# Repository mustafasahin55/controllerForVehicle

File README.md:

# STM32 Tabanlı Motor Kontrol Kartı Özellikleri ve Bağlantıları

## Donanım Özellikleri
1. **PCB Katman Yapısı**:
   1. Katman: Sinyal iletimi için tasarlanmış bakır izler
   2. Katman: Toprak düzlemi (GND)
   3. Katman: Güç dağıtım katmanı (5V/12V)
   4. Katman: İkincil sinyal iletim katmanı

2. **Ana Bileşenler**:
   - STM32F4 serisi mikrodenetleyici (ARM Cortex-M4 çekirdek)
   - PCA9685PW 16-kanallı PWM sürücü entegresi
   - MPU6050 6-eksen IMU sensör (Jiroskop + İvmeölçer)
   - 3x L298N çift motor sürücü modülü

3. **Teknik Parametreler**:
   - PWM Çözünürlüğü: 12-bit (4096 adım)
   - Maksimum Motor Akımı: 2A/channel
   - I2C Haberleşme Hızı: 100kHz/400kHz
   - Çalışma Voltajı: 7-12V DC

## Bağlantı Konfigürasyonu

### STM32-PCA9685PW Arası Bağlantılar
| PCA9685 Pin | STM32 Pin   | İşlev       |
|-------------|-------------|-------------|
| PCA_SCL     | PB6         | I2C1 Clock  |
| PCA_SDA     | PB7         | I2C1 Data   |
| VCC         | 5V          | Güç Besleme|
| GND         | GND         | Toprak      |

### STM32-MPU6050 Arası Bağlantılar
| MPU6050 Pin | STM32 Pin   | İşlev       |
|-------------|-------------|-------------|
| SDA         | PB11        | I2C2 Data   |
| SCL         | PB10        | I2C2 Clock  |
| VCC         | 3.3V        | Güç Besleme|
| GND         | GND         | Toprak      |

### Motor Sürücü Bağlantıları
| L298N Pin   | Bağlantı Noktası | Açıklama               |
|-------------|-------------------|-----------------------|
| IN1-4       | PCA9685 PWM0-3    | Motor kontrol sinyali|
| ENA/ENB     | 5V                | Enable sabit aktif    |
| OUT1-4      | Motor Terminalleri| Motor çıkışları      |
| 12V         | Güç Girişi        | Harici güç kaynağı    |

## Pinout Tablosu
| STM32 Pin | Bağlı Bileşen | İşlev              |
|-----------|---------------|--------------------|
| PA0       | Seri Debug    | UART1_TX           |
| PA1       | Seri Debug    | UART1_RX           |
| PB6-7     | PCA9685       | I2C1 SCL/SDA       |
| PB10-11   | MPU6050       | I2C2 SCL/SDA       |
| PC6-9     | LED Göstergeler| Sistem Durum LED'leri|

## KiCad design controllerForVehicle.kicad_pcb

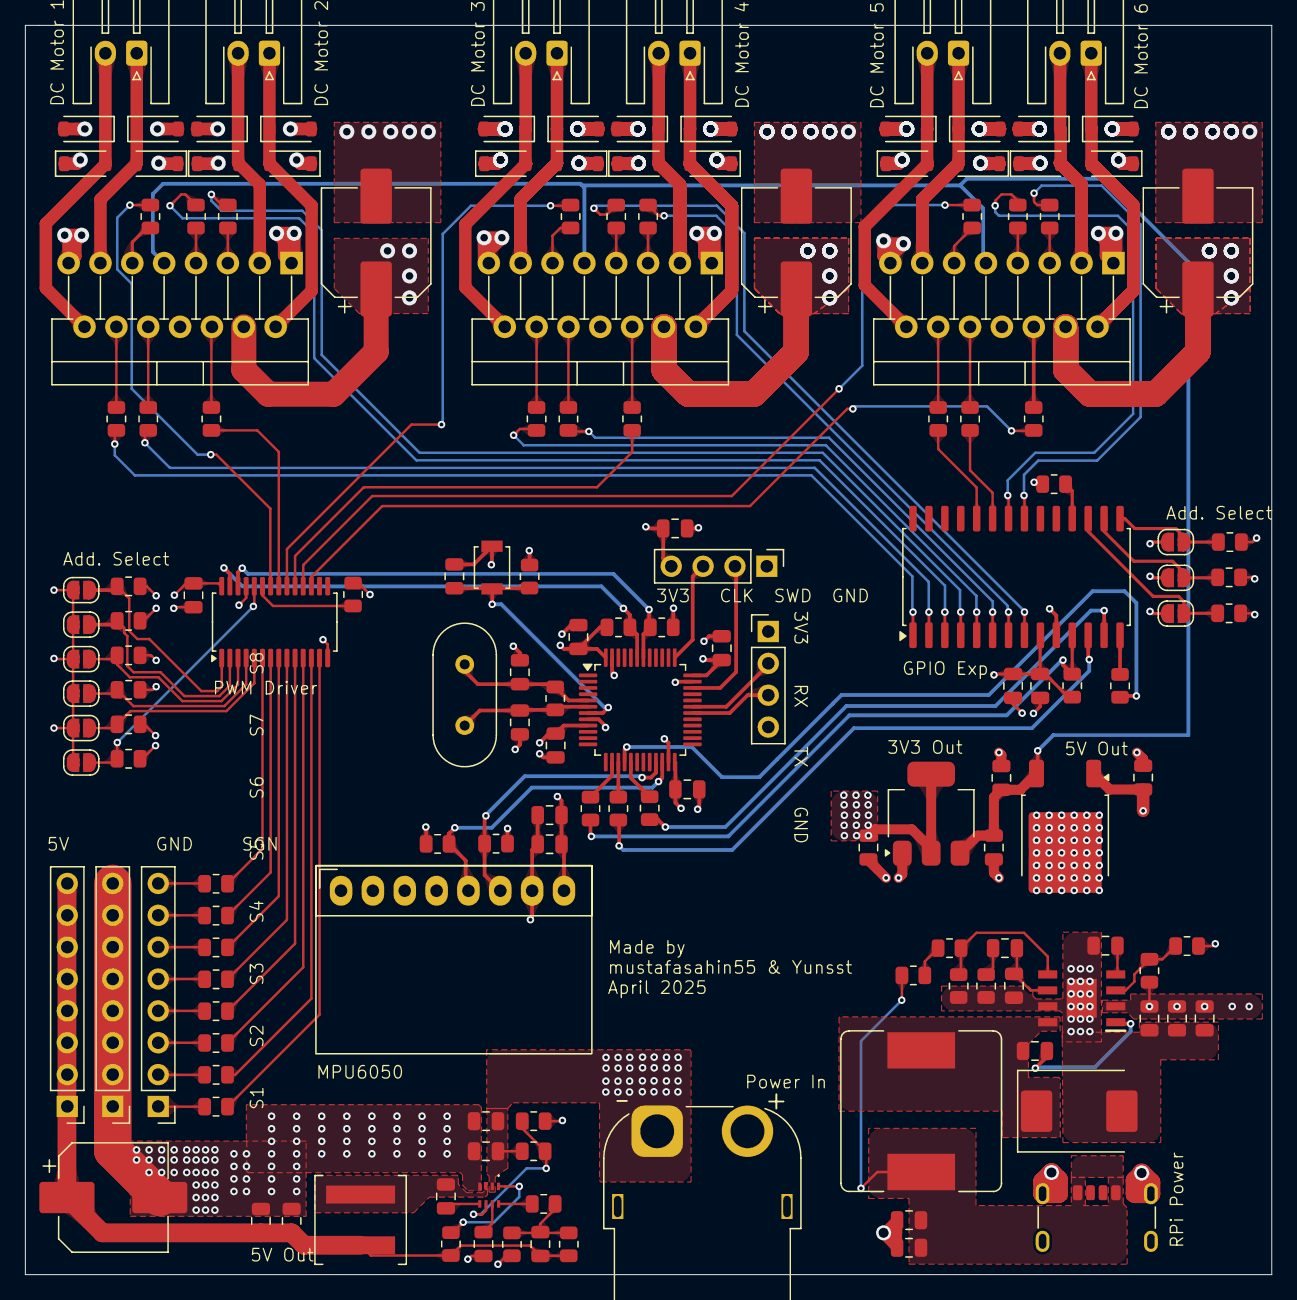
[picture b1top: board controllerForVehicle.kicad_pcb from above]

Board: 4 copper layers, 99.4 x 99.6 mm, 159 parts (0 on the bottom side), 115 nets.

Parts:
C1, C6: 20p; C_0805_2012Metric
C2, C3, C4, C5, C10, C28, C29, C45, C46: 0.1u; C_0805_2012Metric
C7, C8, C11, C12: 220uF 35V; CP_Elec_8x10.5
C9: 1uf; C_0805_2012Metric
C23, C24, C25, C26, C43, C44, C47: 10u; C_0805_2012Metric
C27, C30, C31: 22u; C_0805_2012Metric
C32: 22n; C_0805_2012Metric
C33: 300p; C_0805_2012Metric
C34, C39, C42: 0.01u; C_0805_2012Metric
C35, C36: 47u; C_0805_2012Metric
C37, C38: 4.7u; C_0805_2012Metric
C40: 2200p; C_0805_2012Metric
C41: 22p; C_0805_2012Metric
D1, D2, D3, D4, D5, D6, D7, D8, D9, D10, D11, D12, D13, D14, D15, D16, D17, D18, D19, D20, D21, D22, D23, D24: 1N4007; D_SOD-123
D25: CDBC540-G; D_SMC
IC1: MP2338GTL-Z; MP2338GTLZ
J1: Debug; PinHeader_1x04_P2.54mm_Vertical
J3: VIN; AMASS_XT60PW-F_1x02_P7.20mm_Horizontal
J4, J5, J6: Conn_01x08; PinHeader_1x08_P2.54mm_Vertical
J7, J8, J9, J10, J11, J12: Conn_01x02; JST_XH_S2B-XH-A-1_1x02_P2.50mm_Horizontal
J13: USB_C_Receptacle_PowerOnly_6P; USB_C_Receptacle_GCT_USB4125-xx-x_6P_TopMnt_Horizontal
J14: STM_UART; PinHeader_1x04_P2.54mm_Vertical
JP1, JP7: SJ_A0; SolderJumper-2_P1.3mm_Open_RoundedPad1.0x1.5mm
JP2, JP8: SJ_A1; SolderJumper-2_P1.3mm_Open_RoundedPad1.0x1.5mm
JP3, JP9: SJ_A2; SolderJumper-2_P1.3mm_Open_RoundedPad1.0x1.5mm
JP4: SJ_A3; SolderJumper-2_P1.3mm_Open_RoundedPad1.0x1.5mm
JP5: SJ_A4; SolderJumper-2_P1.3mm_Open_RoundedPad1.0x1.5mm
JP6: SJ_A5; SolderJumper-2_P1.3mm_Open_RoundedPad1.0x1.5mm
L1: MPL-AL6060-6R8; L_Coilcraft_XAL6060-XXX
L2: SRP1265-100M; L_Bourns_SRR1260
PS1: TPS54531DDAR; SOIC127P600X170-9N
R1: 1M; R_0805_2012Metric
R2, R4, R8, R9: 33R; R_0805_2012Metric
R5, R26, R28, R30, R84: 10K; R_0805_2012Metric
R6, R7, R45, R46, R47, R48, R49, R50, R62, R63, R64, R70: 100R; R_0805_2012Metric
R10, R17, R18, R37, R38, R39, R40, R41, R42, R43, R44, R58, R59, R60: 12k; R_0805_2012Metric
R25: 191K; R_0805_2012Metric
R27: 49.9K; R_0805_2012Metric
R29: 90.9k; R_0805_2012Metric
R31: 51.1; R_0805_2012Metric
R32: 665K; R_0805_2012Metric
R33: 10.2k; R_0805_2012Metric
R34: 130K; R_0805_2012Metric
R35: 37.4k; R_0805_2012Metric
R36: 1.96k; R_0805_2012Metric
R51, R52, R53, R54, R55, R56, R57, R61, R65, R66, R67, R68, R72, R77: 10k; R_0805_2012Metric
R69: 4.7K; R_0805_2012Metric
SW1: RESET; SW_SPST_B3U-1000P
U1: STM32F103C8Tx; LQFP-48_7x7mm_P0.5mm
U2, U3, U4: L298N; TO-220-15_P2.54x2.54mm_StaggerOdd_Lead4.58mm_Vertical
U7: L7805; TO-252-2
U8: AMS1117-3.3; SOT-223-3_TabPin2
U9: PCA9685PW; TSSOP-28_4.4x9.7mm_P0.65mm
U10: MPU6050; MPU6050_Breakout
U11: MCP23S17_SO; SOIC-28W_7.5x17.9mm_P1.27mm
Y1: 8mHz; Crystal_HC49-4H_Vertical

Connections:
3V3: C2.2, C3.2, C4.2, C5.2, C10.2, C26.2, C43.1, C44.2, C45.2, C46.2, C47.2, J1.4, J14.1, JP1.1 (A), JP2.1 (A), JP3.1 (A), JP4.1 (A), JP5.1 (A), JP6.1 (A), JP7.1 (A), JP8.1 (A), JP9.1 (A), R5.1, R52.1, R53.1, R66.2, R67.1, R69.1, R84.1, U1.9 (VDDA), U1.24 (VDD), U1.36 (VDD), U1.48 (VDD), U8.2 (VO), U9.28 (VDD), U10.8 (VCC), U11.9 (VDD)
5V1: C24.2, C25.2, U2.9 (Vss), U3.9 (Vss), U4.9 (Vss), U7.3 (OUT), U8.3 (VI)
5V2: C7.1, C30.2, C31.2, C33.1, J5.1, J5.2, J5.3, J5.4, J5.5, J5.6, J5.7, J5.8, L1.2, R26.1, R29.1
5VRPi: C35.2, C36.2, J13.A9 (VBUS), J13.B9 (VBUS), L2.2, R31.1
DC1_1: D17.2 (A), D18.1 (K), J12.1, U4.2 (OUT1)
DC1_2: D19.2 (A), D20.1 (K), J12.2, U4.3 (OUT2)
DC2_1: D21.2 (A), D22.1 (K), J11.1, U4.13 (OUT3)
DC2_2: D23.2 (A), D24.1 (K), J11.2, U4.14 (OUT4)
DC3_1: D1.2 (A), D2.1 (K), J10.1, U2.2 (OUT1)
DC3_2: D3.2 (A), D4.1 (K), J10.2, U2.3 (OUT2)
DC4_1: D5.2 (A), D6.1 (K), J9.1, U2.13 (OUT3)
DC4_2: D7.2 (A), D8.1 (K), J9.2, U2.14 (OUT4)
DC5_1: D9.2 (A), D10.1 (K), J8.1, U3.2 (OUT1)
DC5_2: D11.2 (A), D12.1 (K), J8.2, U3.3 (OUT2)
DC6_1: D13.2 (A), D14.1 (K), J7.1, U3.13 (OUT3)
DC6_2: D15.2 (A), D16.1 (K), J7.2, U3.14 (OUT4)
DCEn1: R59.2, U9.17 (LED10)
DCEn2: R60.2, U9.18 (LED11)
DCEn3: R10.2, U9.19 (LED12)
DCEn4: R17.2, U9.20 (LED13)
DCEn5: R18.2, U9.21 (LED14)
DCEn6: R58.2, U9.22 (LED15)
DCIn1_1: R45.2, U11.21 (GPA0)
DCIn1_2: R46.2, U11.22 (GPA1)
DCIn2_1: R62.2, U11.23 (GPA2)
DCIn2_2: R63.2, U11.24 (GPA3)
DCIn3_1: R7.2, U11.8 (GPB7)
DCIn3_2: R6.2, U11.7 (GPB6)
DCIn4_1: R49.2, U11.6 (GPB5)
DCIn4_2: R50.2, U11.5 (GPB4)
DCIn5_1: R47.2, U11.4 (GPB3)
DCIn5_2: R48.2, U11.3 (GPB2)
DCIn6_1: R64.2, U11.2 (GPB1)
DCIn6_2: R70.2, U11.1 (GPB0)
GND: C1.2, C2.1, C3.1, C4.1, C5.1, C6.2, C7.2, C8.2, C9.1, C10.1, C11.2, C12.2, C23.1, C24.1, C25.1, C26.1, C27.1, C28.1, C30.1, C31.1, C32.1, C35.1, C36.1, C37.1, C38.1, C39.1, C41.1, C42.1, C43.2, C44.1, C45.1, C46.1, C47.1, D2.2 (A), D4.2 (A), D6.2 (A), D8.2 (A), D10.2 (A), D12.2 (A), D14.2 (A), D16.2 (A), D18.2 (A), D20.2 (A), D22.2 (A), D24.2 (A), D25.2 (A), IC1.4 (GND), J1.1, J3.2, J6.1, J6.2, J6.3, J6.4, J6.5, J6.6, J6.7, J6.8, J13.A12 (GND), J13.B12 (GND), J13.S1 (SHIELD), J14.4, PS1.7 (GND), PS1.9 (EP), R27.2, R30.1, R34.2, R35.2, R36.2, R51.1, R54.1, R55.2, R56.1, R57.1, R61.1, R65.1, R68.1, R72.1, R77.1, SW1.1, U1.8 (VSSA), U1.23 (VSS), U1.35 (VSS), U1.47 (VSS), U2.1 (SENSE_A), U2.8 (GND), U2.15 (SENSE_B), U3.1 (SENSE_A), U3.8 (GND), U3.15 (SENSE_B), U4.1 (SENSE_A), U4.8 (GND), U4.15 (SENSE_B), U7.2 (GND), U8.1 (GND), U9.14 (VSS), U9.25 (EXTCLK), U10.7 (GND), U11.10 (VSS)
I2C1_SCL: R53.2, U1.42 (PB6), U9.26 (SCL)
I2C1_SDA: R52.2, U1.43 (PB7), U9.27 (SDA)
I2C2_SCL: R66.1, U1.21 (PB10), U10.6 (SCL)
I2C2_SDA: R67.2, U1.22 (PB11), U10.5 (SDA)
MCP_A0: JP7.2 (B), R68.2, U11.15 (A0)
MCP_A1: JP8.2 (B), R72.2, U11.16 (A1)
MCP_A2: JP9.2 (B), R77.2, U11.17 (A2)
unnamed: C33.2, R28.2, R29.2, R30.2
unnamed: C40.1, R35.1
unnamed: C34.2, D25.1 (K), L2.1, PS1.8 (PH)
unnamed: C29.2, IC1.5 (BST)
unnamed: IC1.6 (EN), R25.2, R27.1
unnamed: IC1.8 (FB), R28.1
unnamed: IC1.1 (PG), R26.2
unnamed: C32.2, IC1.7 (SS)
unnamed: C29.1, IC1.3 (SW), L1.1
unnamed: J4.1, R37.1
unnamed: J4.2, R38.1
unnamed: J4.3, R39.1
unnamed: J4.4, R40.1
unnamed: J4.5, R41.1
unnamed: J4.6, R42.1
unnamed: J4.7, R43.1
unnamed: J4.8, R44.1
unnamed: C34.1, PS1.1 (BOOT)
unnamed: C40.2, C41.2, PS1.6 (COMP)
unnamed: PS1.3 (EN), R32.2, R34.1
unnamed: C42.2, PS1.4 (SS)
unnamed: PS1.5 (VSENSE), R33.2, R36.1
unnamed: R31.2, R33.1
unnamed: R9.2, U1.14 (PA4)
unnamed: R2.1, U1.15 (PA5)
unnamed: R4.1, U1.17 (PA7)
unnamed: R10.1, U2.6 (EnA)
unnamed: R17.1, U2.11 (EnB)
unnamed: R6.1, U2.5 (IN1)
unnamed: R7.1, U2.7 (IN2)
unnamed: R49.1, U2.10 (IN3)
unnamed: R50.1, U2.12 (IN4)
unnamed: R18.1, U3.6 (EnA)
unnamed: R58.1, U3.11 (EnB)
unnamed: R47.1, U3.5 (IN1)
unnamed: R48.1, U3.7 (IN2)
unnamed: R64.1, U3.10 (IN3)
unnamed: R70.1, U3.12 (IN4)
unnamed: R59.1, U4.6 (EnA)
unnamed: R60.1, U4.11 (EnB)
unnamed: R45.1, U4.5 (IN1)
unnamed: R46.1, U4.7 (IN2)
unnamed: R62.1, U4.10 (IN3)
unnamed: R63.1, U4.12 (IN4)
unnamed: R8.2, U11.14 (SO)
unnamed: R84.2, U11.18 (~RESET)
OE: R55.1, U9.23 (~OE)
OSC_IN: C1.1, R1.1, U1.5 (PD0), Y1.2
OSC_OUT: C6.1, R1.2, U1.6 (PD1), Y1.1
PCA_0: R37.2, U9.13 (LED7)
PCA_1: R38.2, U9.12 (LED6)
PCA_2: R39.2, U9.11 (LED5)
PCA_3: R40.2, U9.10 (LED4)
PCA_4: R41.2, U9.9 (LED3)
PCA_5: R42.2, U9.8 (LED2)
PCA_6: R43.2, U9.7 (LED1)
PCA_7: R44.2, U9.6 (LED0)
PCA_A0: JP1.2 (B), R51.2, U9.1 (A0)
PCA_A1: JP2.2 (B), R54.2, U9.2 (A1)
PCA_A2: JP3.2 (B), R56.2, U9.3 (A2)
PCA_A3: JP4.2 (B), R57.2, U9.4 (A3)
PCA_A4: JP5.2 (B), R61.2, U9.5 (A4)
PCA_A5: JP6.2 (B), R65.2, U9.24 (A5)
RESET: C9.2, R5.2, SW1.2, U1.7 (NRST)
SPI1_CS: R9.1, R69.2, U11.11 (~CS)
SPI1_MISO: R8.1, U1.16 (PA6)
SPI1_MOSI: R4.2, U11.13 (SI)
SPI1_SCK: R2.2, U11.12 (SCK)
SWCLK: J1.3, U1.37 (PA14)
SWDIO: J1.2, U1.34 (PA13)
USART1_RX: J14.2, U1.31 (PA10)
USART1_TX: J14.3, U1.30 (PA9)
VIN: C8.1, C11.1, C12.1, C23.2, C27.2, C28.2, C37.2, C38.2, C39.2, D1.1 (K), D3.1 (K), D5.1 (K), D7.1 (K), D9.1 (K), D11.1 (K), D13.1 (K), D15.1 (K), D17.1 (K), D19.1 (K), D21.1 (K), D23.1 (K), IC1.2 (VIN), J3.1, PS1.2 (VIN), R25.1, R32.1, U2.4 (Vs), U3.4 (Vs), U4.4 (Vs), U7.1 (IN)

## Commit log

2025-02-07 power regulators added
2025-02-12 DC motor drivers added
2025-02-12 DC motor zener rev.
    Zener diode value in dc motor was changed to BZV55 5.1V
2025-02-12 stm32 added
2025-02-12 DC motor driver revised
2025-02-12 DC motor driver revised
    l298n Vss->5v
2025-02-12 added components
    servo controller, esp32
2025-02-14 some connectors added
2025-02-15 gpio expander added comm finished
2025-02-16 Visual Improvements
2025-02-17 schematic finished
2025-03-19 Routing
    Routing STM32 and Components
2025-03-19 Routing
    Routing ESP32 and Components
2025-03-20 Routing ESP32 and Components
2025-03-20 Power Routing
2025-03-21 placing completed.
2025-03-28 silinecek
2025-04-01 Revert "placing completed."
    This reverts commit 8fc8ab54a7d5bb0e004d046318c33d8a5f2fb8c8.
2025-04-01 Reapply "placing completed."
    This reverts commit 83f85ef5575867dc78eeeae3514badb4960c2205.
2025-04-03 esp32 silindi, yerleştirmeler yapıldı
2025-04-04 dc sürücü yol çizimleri yapıldı
2025-04-04 yerleştirmeler devam
2025-04-04 17.45
2025-04-04 Routing
2025-04-04 yerleştirme tamamlandı
    3d modeller eklenecek
    drc kontrolü yapılacak
2025-04-04 visuals completed
    drc check kaldı
2025-04-04 texts added
